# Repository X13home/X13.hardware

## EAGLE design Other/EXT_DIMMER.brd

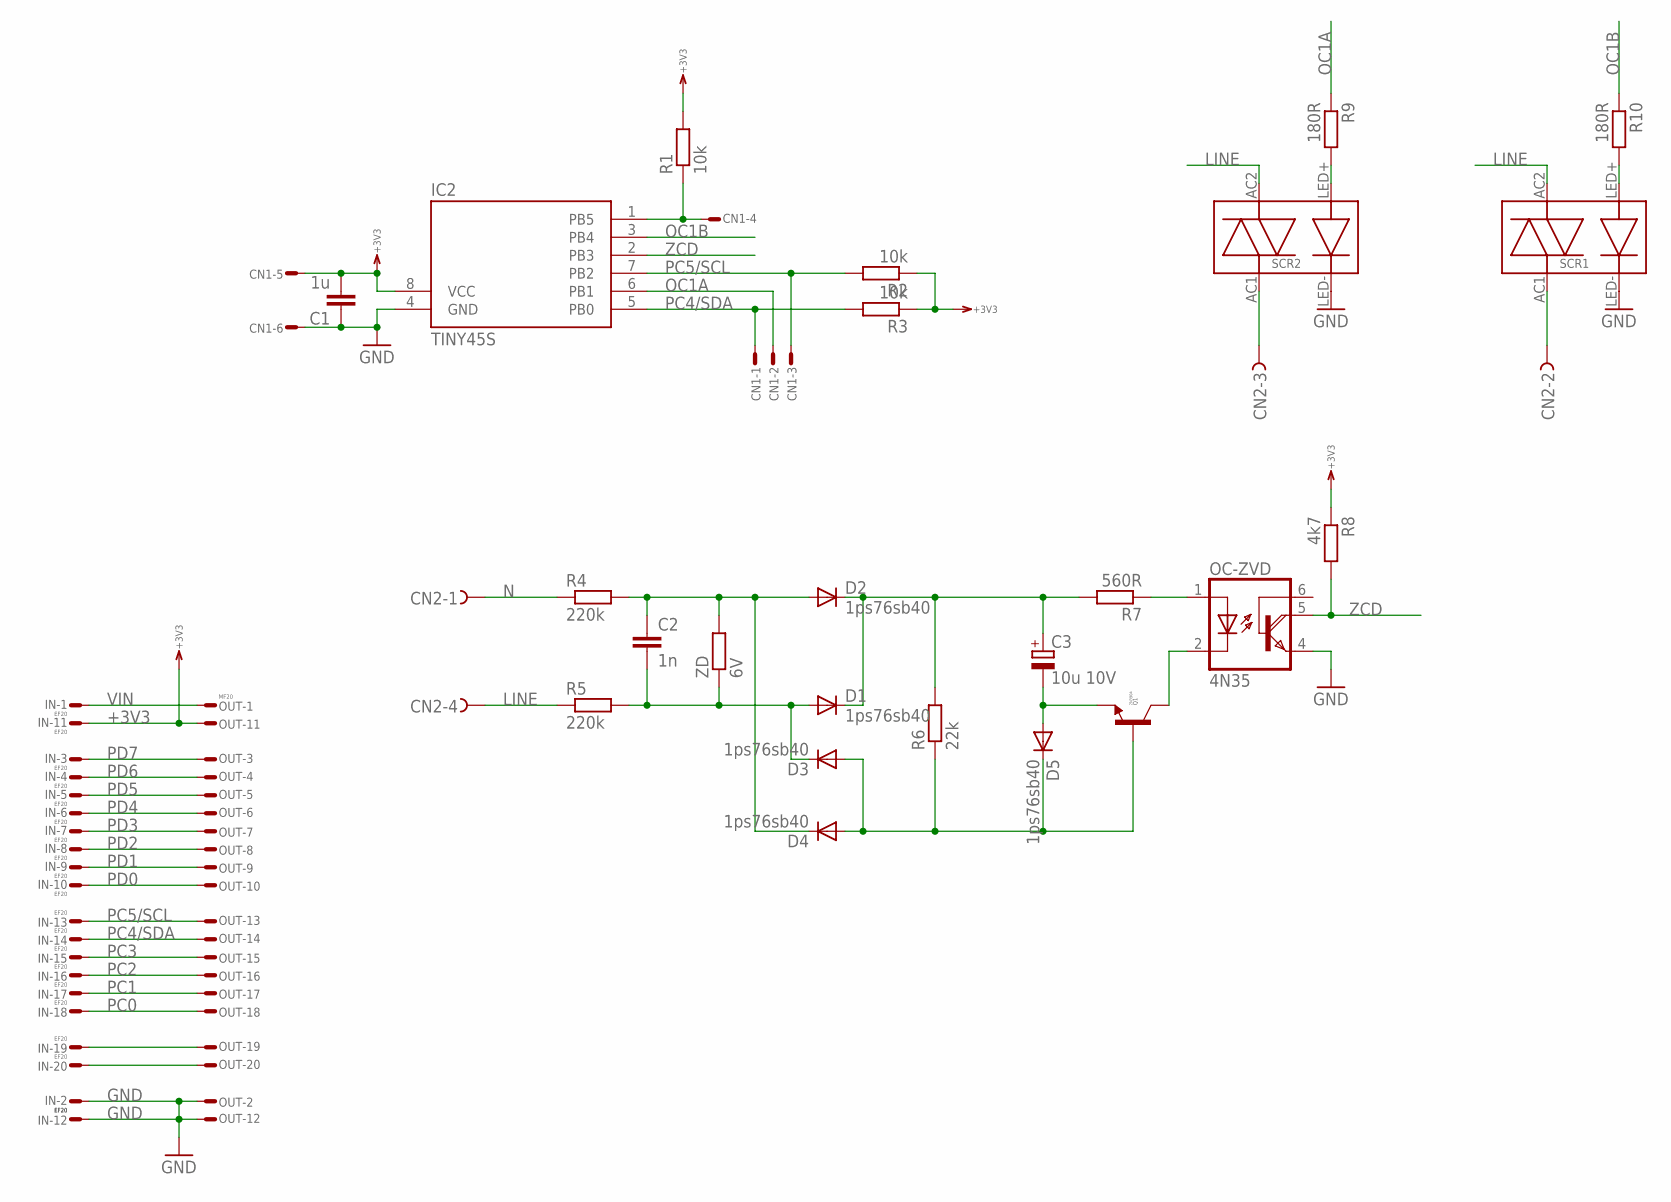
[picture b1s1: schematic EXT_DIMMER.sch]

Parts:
C1: 1u; 0603
C2: 1n; 1206
C3: 10u 10V; SMC_A
CN1: CON6N; CON6
CN2: CON4-S; CTB9308
D1, D2, D3, D4, D5: 1ps76sb40; SOD323
IC2: TINY45S; SOIC8
IN: EF20; FE10-2WSS
OC-ZVD: 4N35; DIL06
OUT: MF20; ML20LS
Q1: 2N3904; SOT23
R1, R2, R3: 10k; 0603
R4, R5: 220k; 1206
R6: 22k; 0603
R7: 560R; 0603
R8: 4k7; 0603
R9, R10: 180R; 0603
SCR1, SCR2: S202
ZD: 6V; 1206

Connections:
+3V3: C1.2, CN1.5, IC2.8 (VCC), IN.P$11, OUT.P$11, R1.2, R2.1, R3.1, R8.1
GND: C1.1, CN1.6, IC2.4 (GND), IN.P$2, IN.P$12, OC-ZVD.4 (E), OUT.P$2, OUT.P$12, SCR1.LED- (L-), SCR2.LED- (L-)
LINE: CN2.-4, R5.1, SCR1.AC2, SCR2.AC2
N: CN2.-1, R4.1
unnamed: IN.P$20, OUT.P$20
unnamed: CN1.4, IC2.1 (PB5), R1.1
unnamed: IN.P$19, OUT.P$19
unnamed: C2.1, D2.A, D4.C, R4.2, ZD.2
unnamed: C2.2, D1.A, D3.C, R5.2, ZD.1
unnamed: C3.+, D1.C, D2.C, R6.2, R7.2
unnamed: D3.A, D4.A, D5.C, Q1.1 (B), R6.1
unnamed: OC-ZVD.1 (A), R7.1
unnamed: C3.-, D5.A, Q1.2 (E)
unnamed: OC-ZVD.2 (C), Q1.3 (C)
unnamed: R9.2, SCR2.LED+ (L+)
unnamed: R10.2, SCR1.LED+ (L+)
unnamed: CN2.-3, SCR2.AC1
unnamed: CN2.-2, SCR1.AC1
OC1A: CN1.2, IC2.6 (PB1), R9.1
OC1B: IC2.3 (PB4), R10.1
PC0: IN.P$18, OUT.P$18
PC1: IN.P$17, OUT.P$17
PC2: IN.P$16, OUT.P$16
PC3: IN.P$15, OUT.P$15
PC4/SDA: CN1.1, IC2.5 (PB0), IN.P$14, OUT.P$14, R3.2
PC5/SCL: CN1.3, IC2.7 (PB2), IN.P$13, OUT.P$13, R2.2
PD0: IN.P$10, OUT.P$10
PD1: IN.P$9, OUT.P$9
PD2: IN.P$8, OUT.P$8
PD3: IN.P$7, OUT.P$7
PD4: IN.P$6, OUT.P$6
PD5: IN.P$5, OUT.P$5
PD6: IN.P$4, OUT.P$4
PD7: IN.P$3, OUT.P$3
VIN: IN.P$1, OUT.P$1
ZCD: IC2.2 (PB3), OC-ZVD.5 (COL), R8.2

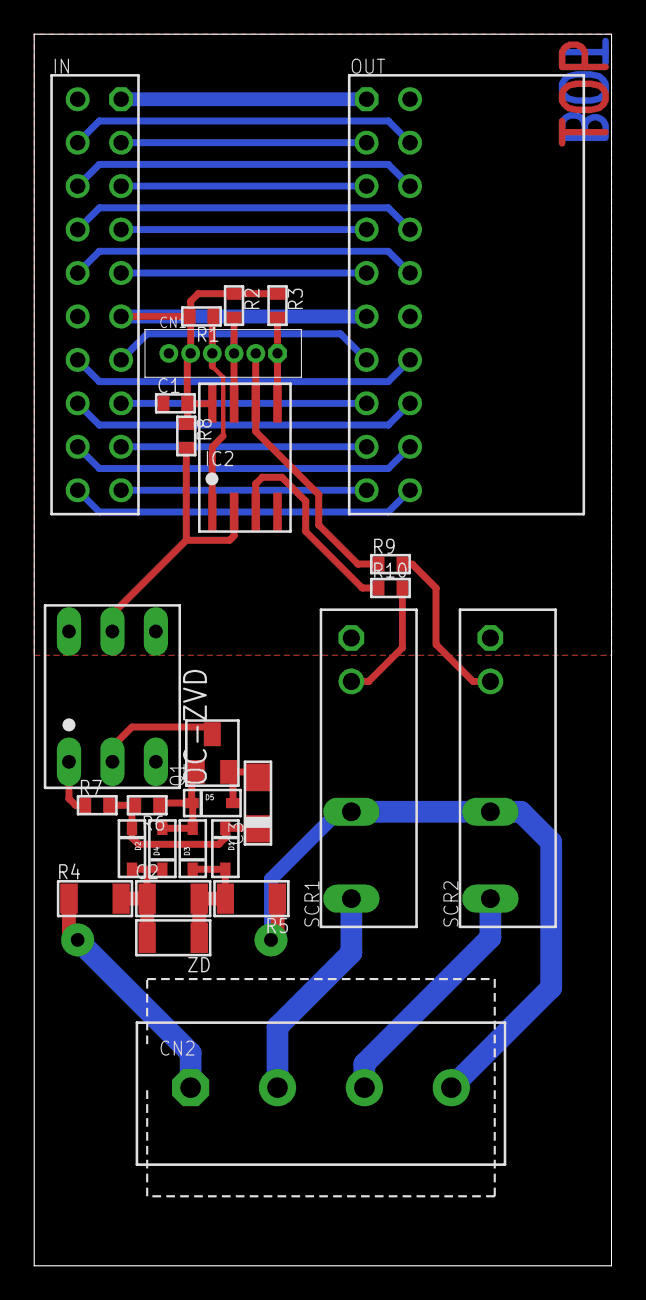
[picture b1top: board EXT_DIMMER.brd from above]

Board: 2 copper layers, 33.8 x 72.0 mm, 28 parts (0 on the bottom side), 36 nets.

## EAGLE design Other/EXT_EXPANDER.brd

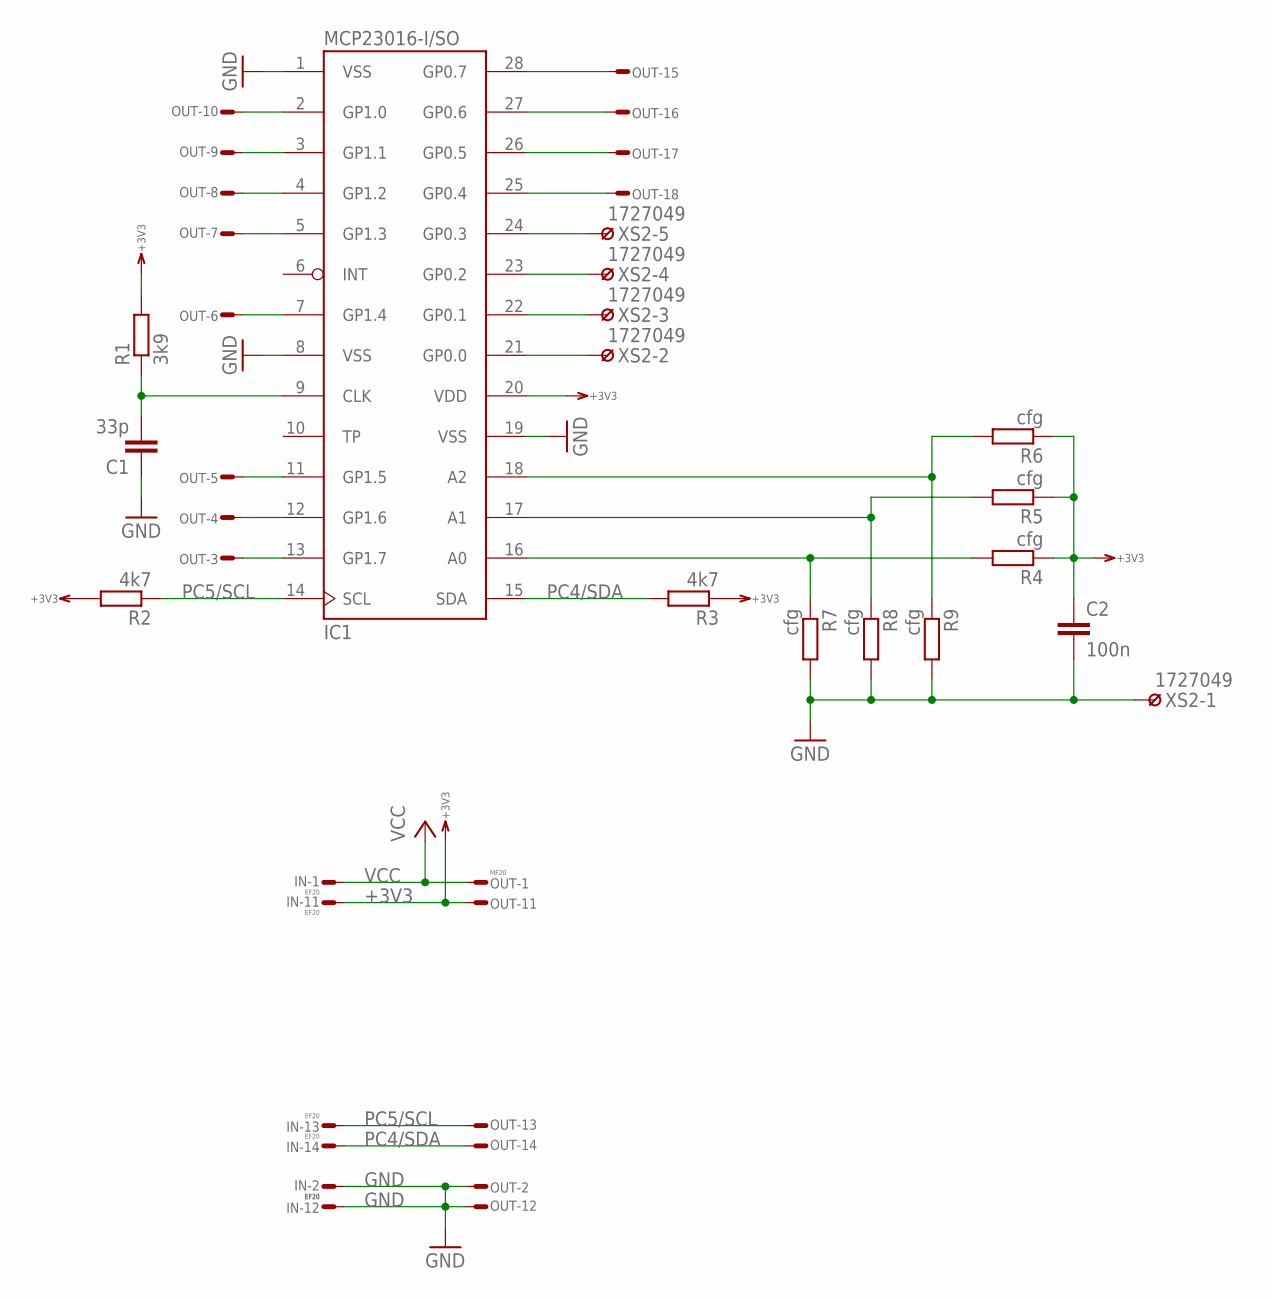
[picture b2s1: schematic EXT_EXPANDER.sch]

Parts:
C1: 33p; 0603
C2: 100n; 0603
IC1: MCP23016-I/SO; SOIC28
IN: EF20; FE10-2WS
OUT: MF20; ML20LS
R1: 3k9; 0603
R2, R3: 4k7; 0603
R4, R5, R6, R7, R8, R9: cfg; 0603
XS2: 1727049

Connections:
+3V3: C2.1, IC1.20 (VDD), IN.P$11, OUT.P$11, R1.2, R2.2, R3.1, R4.1, R5.1, R6.1; also elsewhere on the board
GND: C1.1, C2.2, IC1.1 (VSS), IC1.8 (VSS), IC1.19 (VSS), IN.P$2, IN.P$12, OUT.P$2, OUT.P$12, R7.2, R8.2, R9.2, XS2.1; also elsewhere on the board
unnamed: C1.2, IC1.9 (CLK), R1.1
unnamed: IC1.7 (GP1.4), OUT.P$6
unnamed: IC1.5 (GP1.3), OUT.P$7
unnamed: IC1.4 (GP1.2), OUT.P$8
unnamed: IC1.3 (GP1.1), OUT.P$9
unnamed: IC1.2 (GP1.0), OUT.P$10
unnamed: IC1.11 (GP1.5), OUT.P$5
unnamed: IC1.12 (GP1.6), OUT.P$4
unnamed: IC1.13 (GP1.7), OUT.P$3
unnamed: IC1.16 (A0), R4.2, R7.1
unnamed: IC1.17 (A1), R5.2, R8.1
unnamed: IC1.18 (A2), R6.2, R9.1
unnamed 14: IC1.21 (GP0.0), XS2.2; also elsewhere on the board
unnamed 15: IC1.22 (GP0.1), XS2.3; also elsewhere on the board
unnamed 16: IC1.23 (GP0.2), XS2.4; also elsewhere on the board
unnamed 17: IC1.24 (GP0.3), XS2.5; also elsewhere on the board
unnamed: IC1.25 (GP0.4), OUT.P$18
unnamed: IC1.26 (GP0.5), OUT.P$17
unnamed: IC1.27 (GP0.6), OUT.P$16
unnamed: IC1.28 (GP0.7), OUT.P$15
PC4/SDA: IC1.15 (SDA), IN.P$14, OUT.P$14, R3.2
PC5/SCL: IC1.14 (SCL), IN.P$13, OUT.P$13, R2.1
VCC: IN.P$1, OUT.P$1

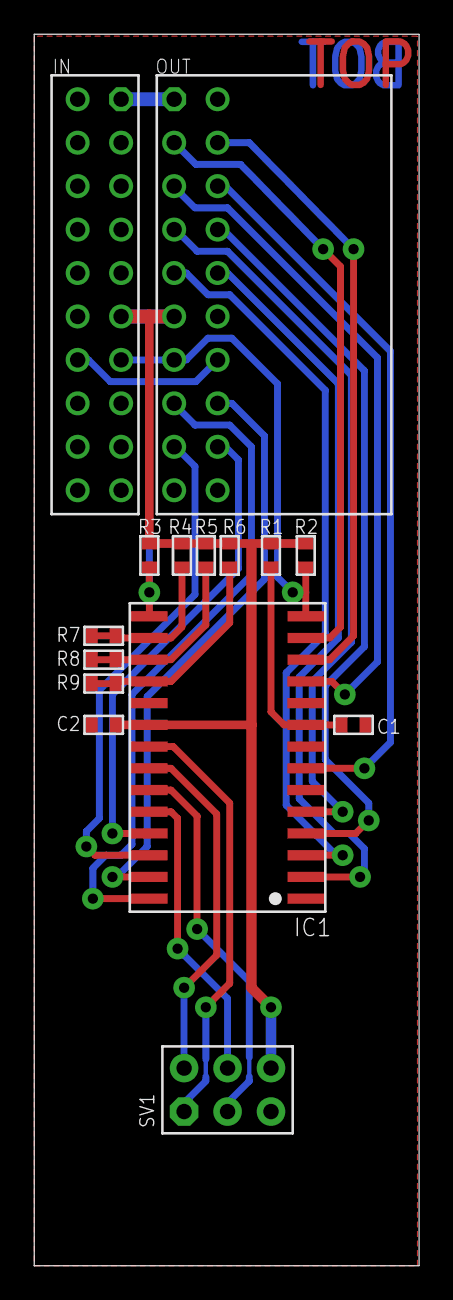
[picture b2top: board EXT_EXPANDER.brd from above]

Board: 2 copper layers, 22.5 x 72.0 mm, 15 parts (0 on the bottom side), 25 nets.

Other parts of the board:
SV1: ML6S

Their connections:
+3V3: SV1.6; also elsewhere on the board
GND: SV1.5; also elsewhere on the board
unnamed 14: SV1.1; also elsewhere on the board
unnamed 15: SV1.2; also elsewhere on the board
unnamed 16: SV1.3; also elsewhere on the board
unnamed 17: SV1.4; also elsewhere on the board

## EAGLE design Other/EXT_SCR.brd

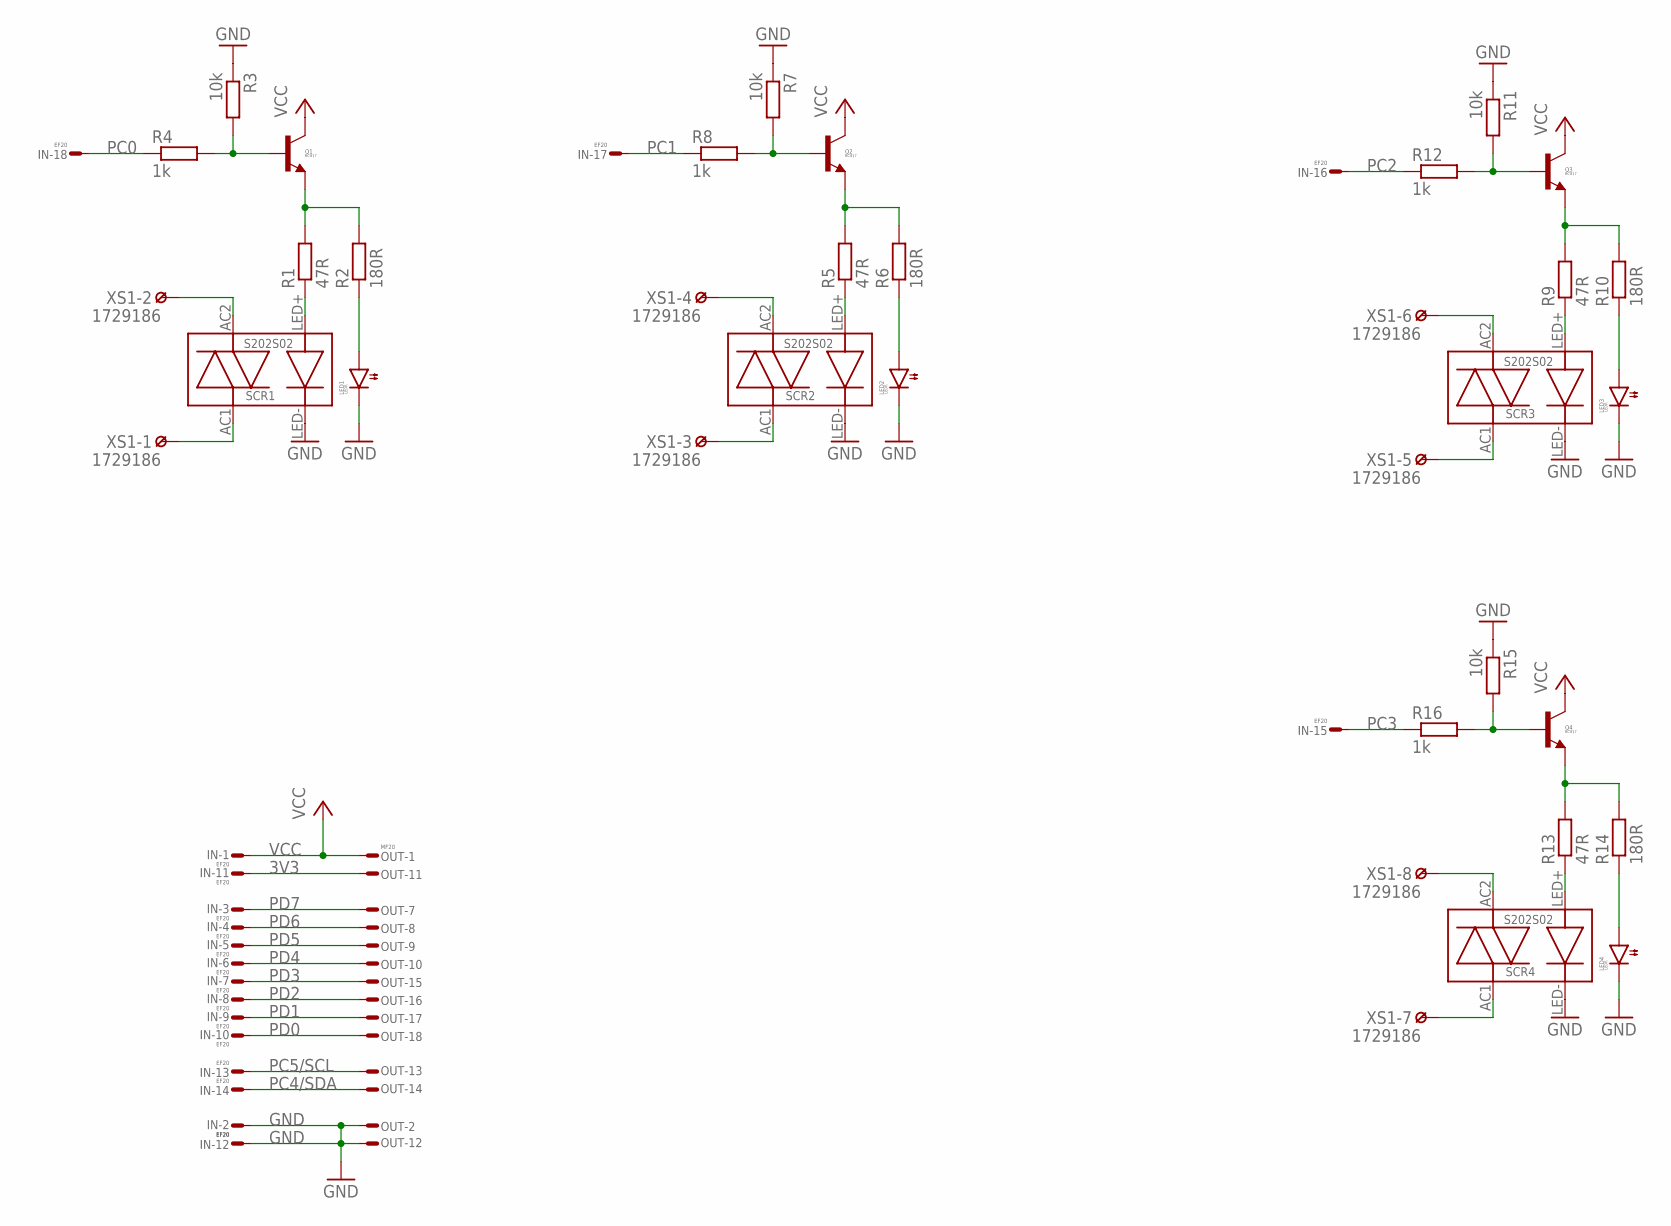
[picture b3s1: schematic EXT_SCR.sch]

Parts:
IN: EF20; FE10-2WSS
LED1, LED2, LED3, LED4: LEDR; 1206
OUT: MF20; ML20LS
Q1, Q2, Q3, Q4: BC817; SOT23
R1, R5, R9, R13: 47R; 0603
R2, R6, R10, R14: 180R; 0603
R3, R7, R11, R15: 10k; 0603
R4, R8, R12, R16: 1k; 0603
SCR1, SCR2, SCR3, SCR4: S202S02; S202
XS1: 1729186; W237-8P

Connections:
3V3: IN.P$11, OUT.P$11
GND: IN.P$2, IN.P$12, LED1.2 (C), LED2.2 (C), LED3.2 (C), LED4.2 (C), OUT.P$2, OUT.P$12, R3.1, R7.1, R11.1, R15.1, SCR1.LED- (L-), SCR2.LED- (L-), SCR3.LED- (L-), SCR4.LED- (L-)
unnamed: R1.1, SCR1.LED+ (L+)
unnamed: LED1.1 (A), R2.1
unnamed: Q1.2 (E), R1.2, R2.2
unnamed: Q1.1 (B), R3.2, R4.2
unnamed: R5.1, SCR2.LED+ (L+)
unnamed: LED2.1 (A), R6.1
unnamed: Q2.2 (E), R5.2, R6.2
unnamed: Q2.1 (B), R7.2, R8.2
unnamed: R9.1, SCR3.LED+ (L+)
unnamed: LED3.1 (A), R10.1
unnamed: Q3.2 (E), R9.2, R10.2
unnamed: Q3.1 (B), R11.2, R12.2
unnamed: R13.1, SCR4.LED+ (L+)
unnamed: LED4.1 (A), R14.1
unnamed: Q4.2 (E), R13.2, R14.2
unnamed: Q4.1 (B), R15.2, R16.2
unnamed: SCR1.AC1, XS1.1
unnamed: SCR1.AC2, XS1.2
unnamed: SCR2.AC1, XS1.3
unnamed: SCR2.AC2, XS1.4
unnamed: SCR3.AC1, XS1.5
unnamed: SCR3.AC2, XS1.6
unnamed: SCR4.AC2, XS1.8
unnamed: SCR4.AC1, XS1.7
PC0: IN.P$18, R4.1
PC1: IN.P$17, R8.1
PC2: IN.P$16, R12.1
PC3: IN.P$15, R16.1
PC4/SDA: IN.P$14, OUT.P$14
PC5/SCL: IN.P$13, OUT.P$13
PD0: IN.P$10, OUT.P$18
PD1: IN.P$9, OUT.P$17
PD2: IN.P$8, OUT.P$16
PD3: IN.P$7, OUT.P$15
PD4: IN.P$6, OUT.P$10
PD5: IN.P$5, OUT.P$9
PD6: IN.P$4, OUT.P$8
PD7: IN.P$3, OUT.P$7
VCC: IN.P$1, OUT.P$1, Q1.3 (C), Q2.3 (C), Q3.3 (C), Q4.3 (C)

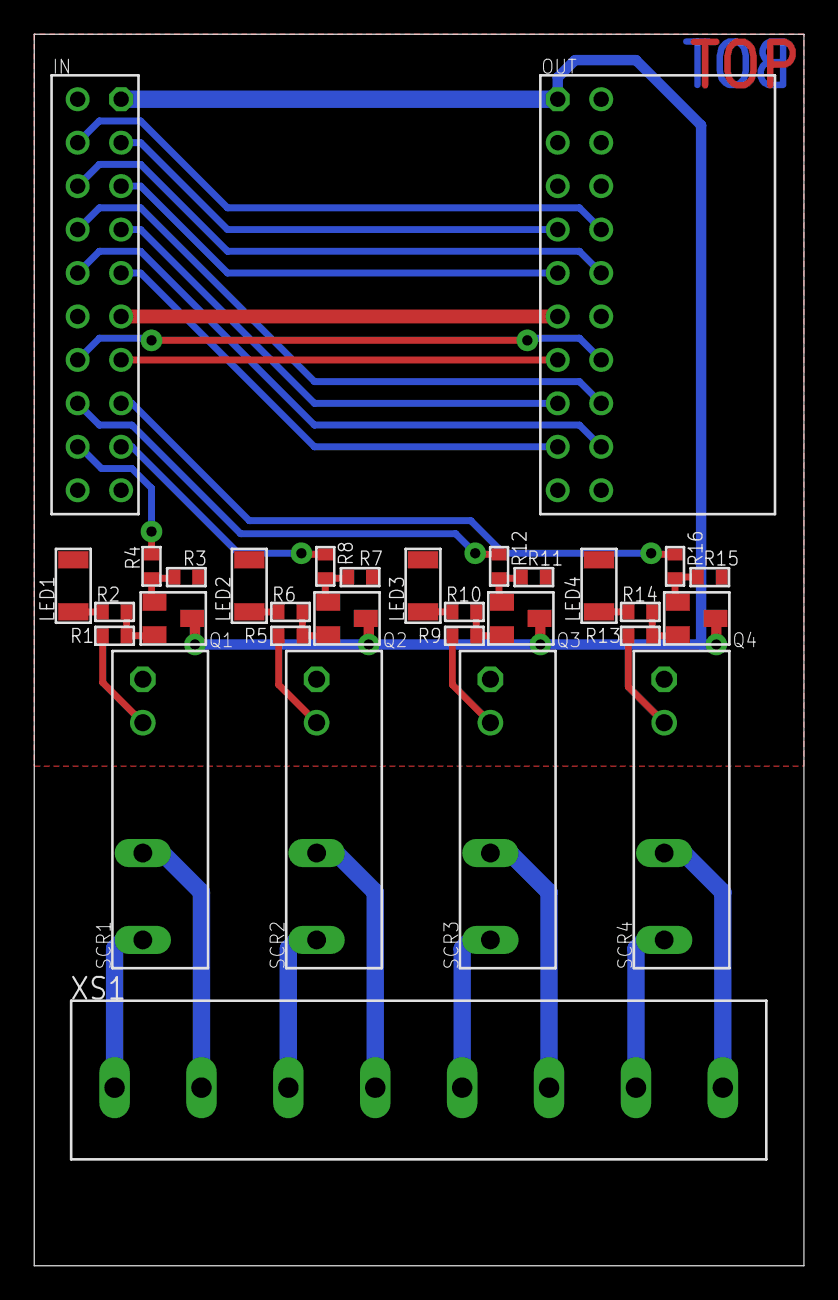
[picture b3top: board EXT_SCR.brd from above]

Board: 2 copper layers, 45.0 x 72.0 mm, 31 parts (0 on the bottom side), 41 nets.

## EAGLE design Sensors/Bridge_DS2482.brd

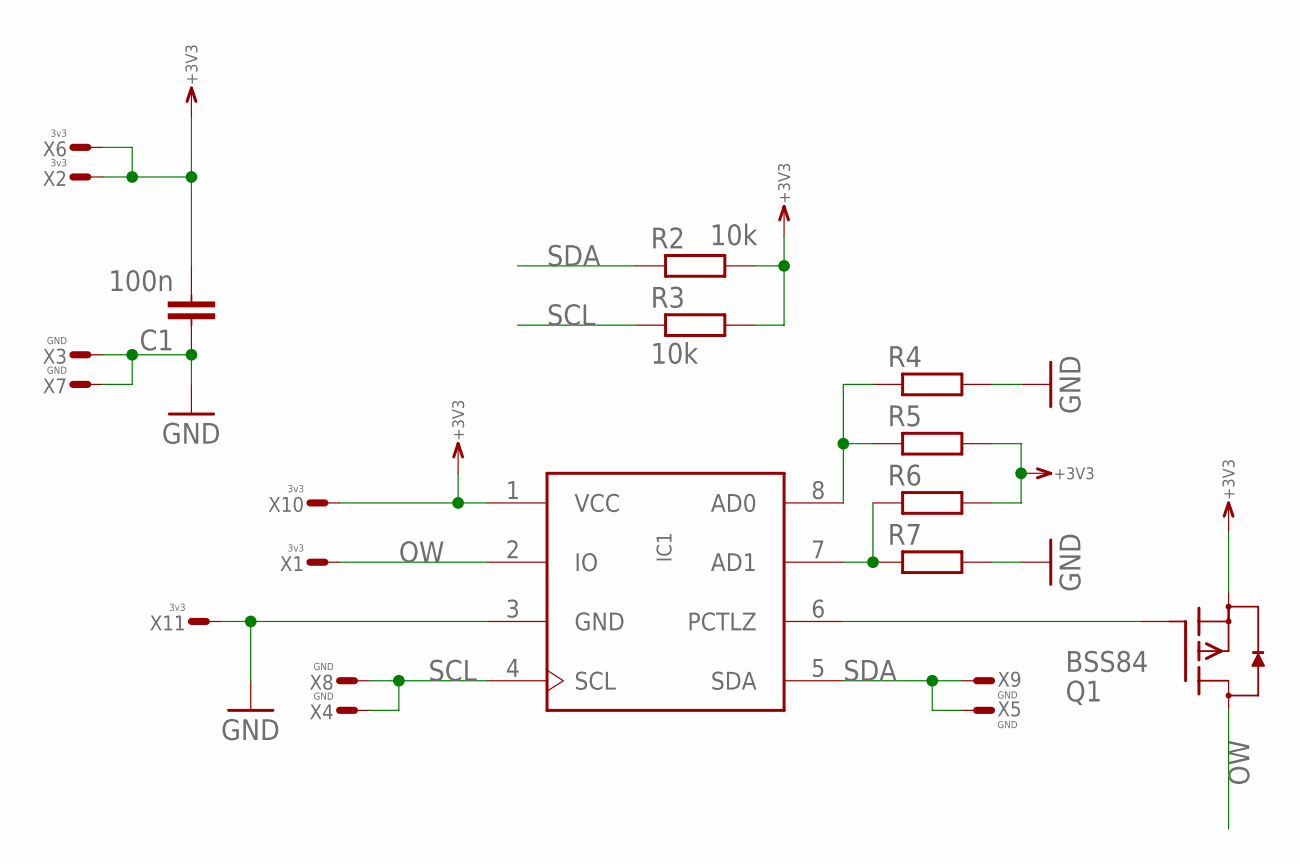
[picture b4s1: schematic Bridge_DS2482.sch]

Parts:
C1: 100n; 0603
IC1: DS2482S; SO8
Q1: BSS84; SOT23
R2, R3: 10k; 0603
R4, R5, R6, R7: R0603; 0603
X1, X2, X6, X10, X11: 3v3; T1.6/0.9
X3, X4, X5, X7, X8, X9: GND; T1.6/0.9

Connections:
+3V3: C1.2, IC1.1 (VCC), Q1.2 (S), R2.2, R3.2, R5.2, R6.2, X2.1, X6.1, X10.1
GND: C1.1, IC1.3 (GND), R4.2, R7.2, X3.1, X7.1, X11.1
unnamed: IC1.7 (AD1), R6.1, R7.1
unnamed: IC1.8 (AD0), R4.1, R5.1
unnamed: IC1.6 (PCTLZ), Q1.1 (G)
OW: IC1.2 (IO), Q1.3 (D), X1.1
SCL: IC1.4 (SCL), R3.1, X4.1, X8.1
SDA: IC1.5 (SDA), R2.1, X5.1, X9.1

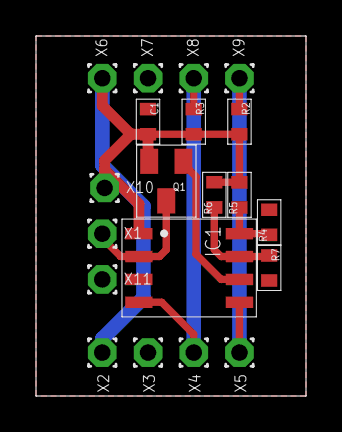
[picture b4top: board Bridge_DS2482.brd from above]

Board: 2 copper layers, 15.0 x 20.0 mm, 20 parts (0 on the bottom side), 8 nets.

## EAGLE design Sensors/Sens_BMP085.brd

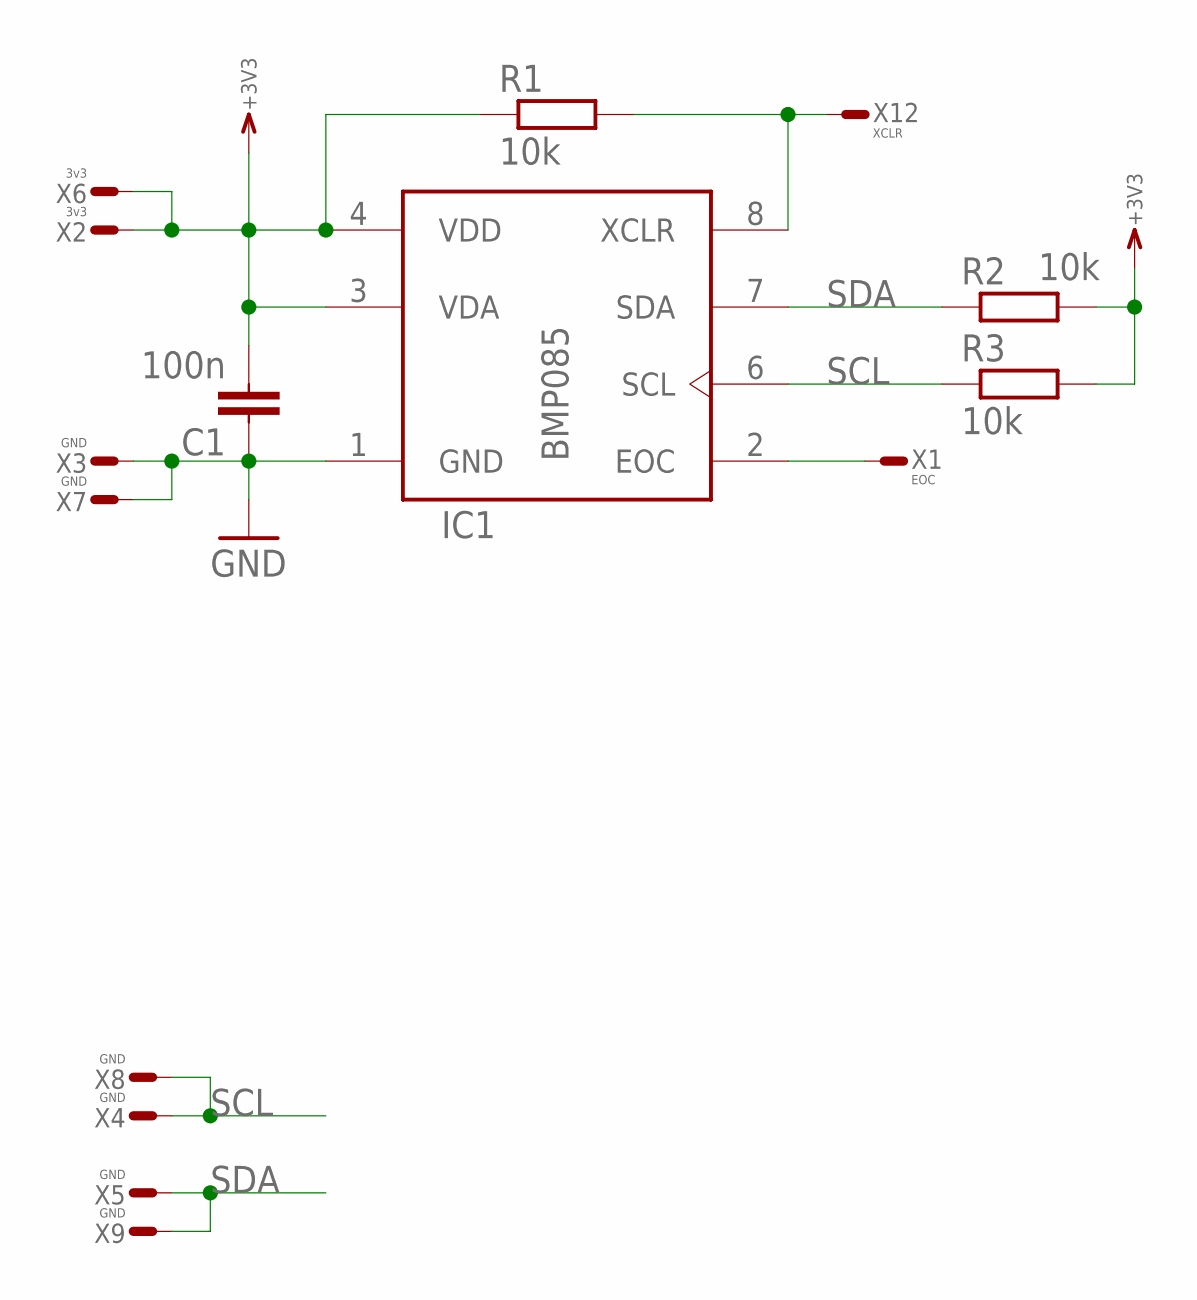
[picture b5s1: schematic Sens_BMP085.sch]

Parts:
C1: 100n; 0603
IC1: BMP085; LCC8
R1, R2, R3: 10k; 0603
X1: EOC; S1.27R
X2, X6: 3v3; T1.6/0.9
X3, X4, X5, X7, X8, X9: GND; T1.6/0.9
X12: XCLR; S1.27R

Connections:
+3V3: C1.2, IC1.3 (VDA), IC1.4 (VDD), R1.1, R2.2, R3.2, X2.1, X6.1
EOC: IC1.2 (EOC), X1.1
GND: C1.1, IC1.1 (GND), X3.1, X7.1
SCL: IC1.6 (SCL), R3.1, X4.1, X8.1
SDA: IC1.7 (SDA), R2.1, X5.1, X9.1
XCLR: IC1.8 (XCLR), R1.2, X12.1

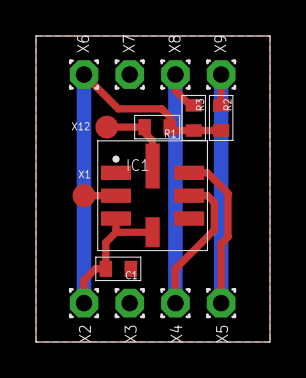
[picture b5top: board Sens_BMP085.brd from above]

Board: 2 copper layers, 13.0 x 17.0 mm, 15 parts (0 on the bottom side), 6 nets.

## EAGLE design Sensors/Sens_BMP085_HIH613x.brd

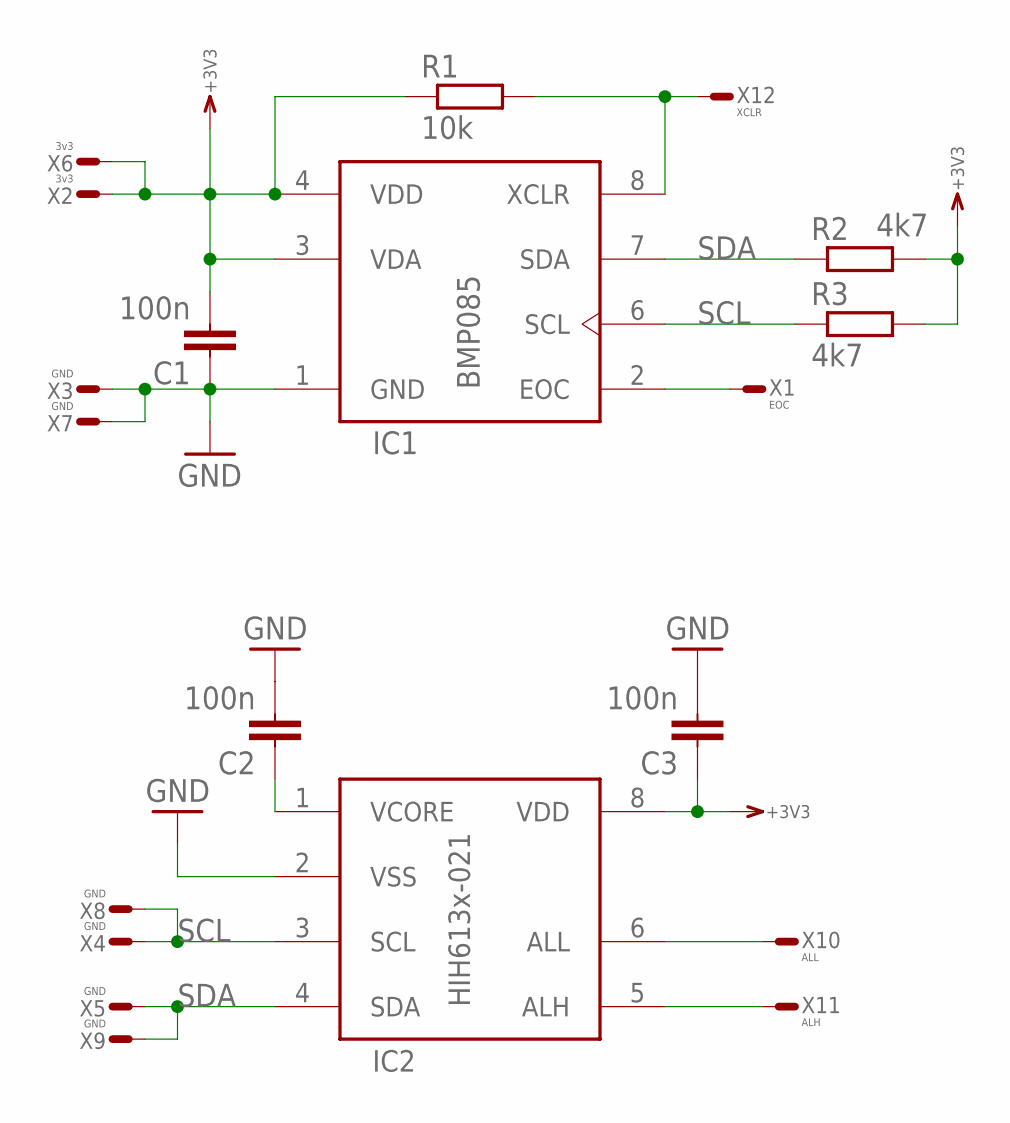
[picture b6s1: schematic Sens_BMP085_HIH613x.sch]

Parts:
C1, C2, C3: 100n; 0603
IC1: BMP085; LCC8
IC2: HIH613x-021; SO8
R1: 10k; 0603
R2, R3: 4k7; 0603
X1: EOC; S1.27R
X2, X6: 3v3; T1.6/0.9
X3, X4, X5, X7, X8, X9: GND; T1.6/0.9
X10: ALL; S1.27R
X11: ALH; S1.27R
X12: XCLR; S1.27R

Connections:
+3V3: C1.2, C3.1, IC1.3 (VDA), IC1.4 (VDD), IC2.8 (VDD), R1.1, R2.2, R3.2, X2.1, X6.1
ALH: IC2.5 (ALH), X11.1
ALL: IC2.6 (ALL), X10.1
EOC: IC1.2 (EOC), X1.1
GND: C1.1, C2.2, C3.2, IC1.1 (GND), IC2.2 (VSS), X3.1, X7.1
unnamed: C2.1, IC2.1 (VCORE)
SCL: IC1.6 (SCL), IC2.3 (SCL), R3.1, X4.1, X8.1
SDA: IC1.7 (SDA), IC2.4 (SDA), R2.1, X5.1, X9.1
XCLR: IC1.8 (XCLR), R1.2, X12.1

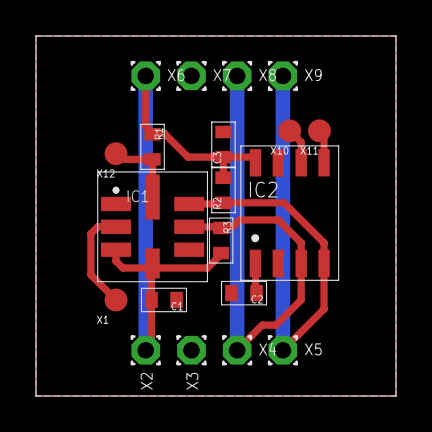
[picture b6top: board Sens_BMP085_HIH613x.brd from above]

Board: 2 copper layers, 20.0 x 20.0 mm, 20 parts (0 on the bottom side), 9 nets.

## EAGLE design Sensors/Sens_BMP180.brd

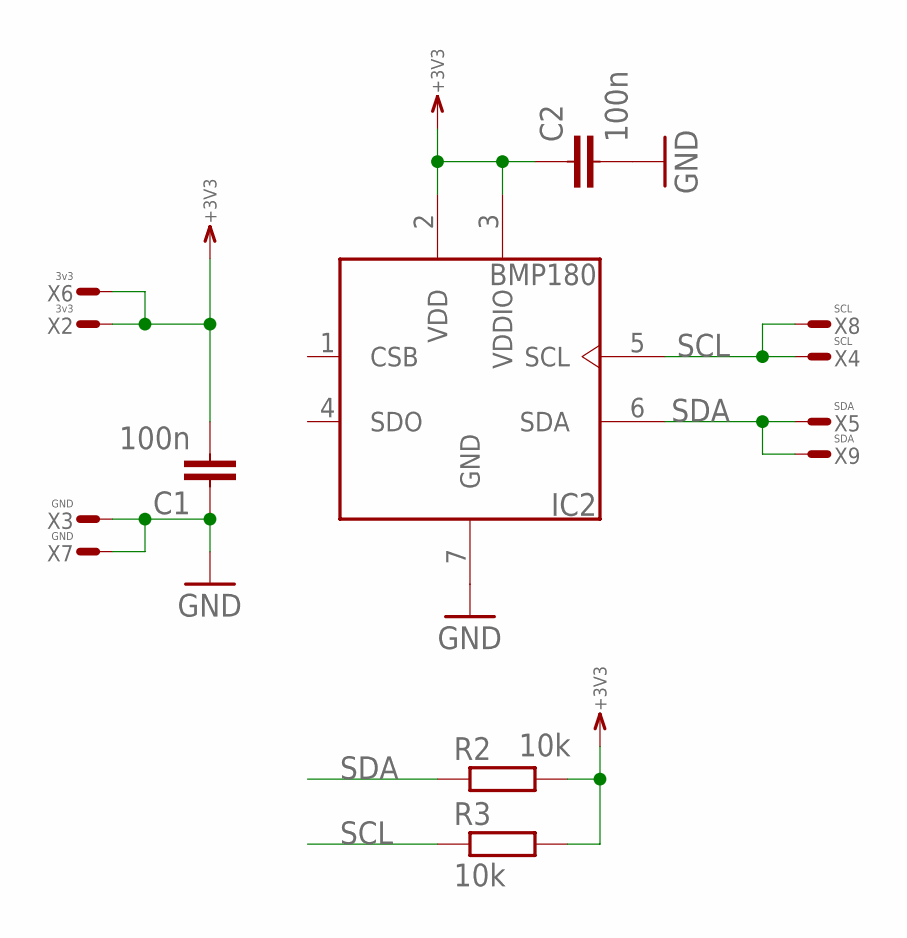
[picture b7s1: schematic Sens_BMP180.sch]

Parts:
C1, C2: 100n; 0603
IC2: BMP180; 7-VELGA
R2, R3: 10k; 0603
X2, X6: 3v3; T1.6/0.9
X3, X7: GND; T1.6/0.9
X4, X8: SCL; T1.6/0.9
X5, X9: SDA; T1.6/0.9

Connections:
+3V3: C1.2, C2.1, IC2.2 (VDD), IC2.3 (VDDIO), R2.2, R3.2, X2.1, X6.1
GND: C1.1, C2.2, IC2.7 (GND), X3.1, X7.1
SCL: IC2.5 (SCL), R3.1, X4.1, X8.1
SDA: IC2.6 (SDA), R2.1, X5.1, X9.1

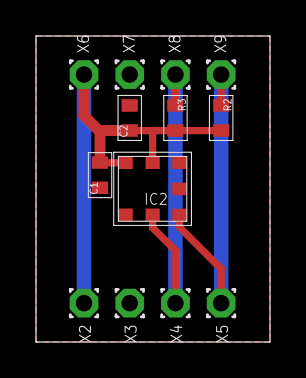
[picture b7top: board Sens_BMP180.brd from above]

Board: 2 copper layers, 13.0 x 17.0 mm, 13 parts (0 on the bottom side), 4 nets.
